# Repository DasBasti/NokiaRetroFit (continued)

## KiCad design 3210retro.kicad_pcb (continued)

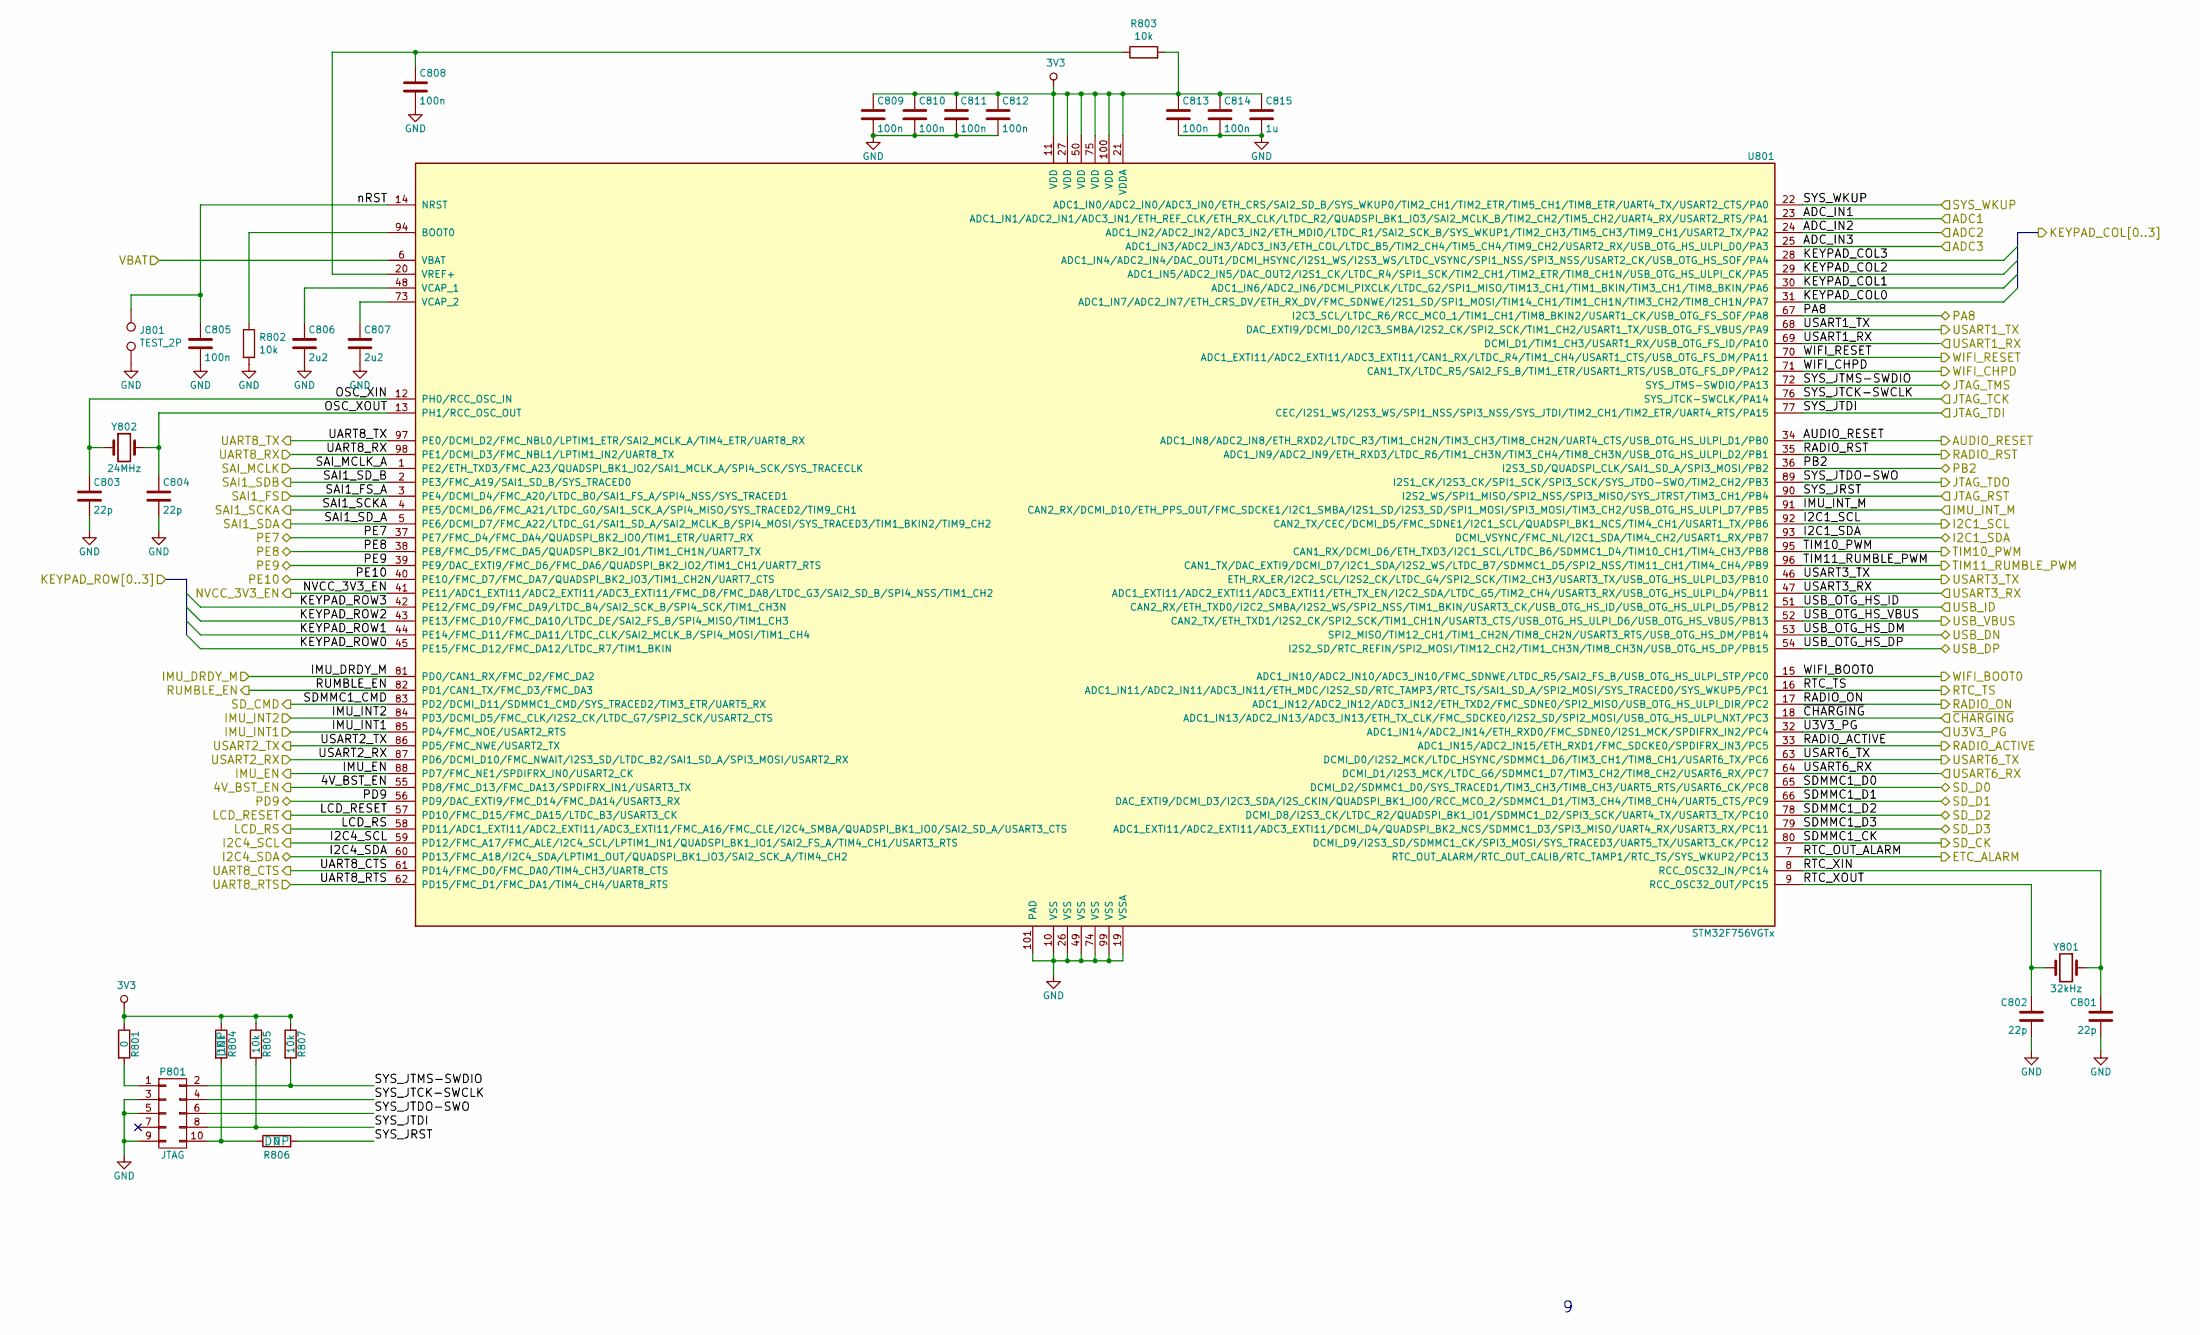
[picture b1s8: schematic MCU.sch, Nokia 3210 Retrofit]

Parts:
C801, C802, C803, C804: 22p; C_0402_NoSilk
C805, C808, C809, C810, C811, C812, C813, C814: 100n; C_0402_NoSilk
C806, C807: 2u2; C_0402_NoSilk
C815: 1u; C_0402_NoSilk
J801: TEST_2P; SolderWirePad_2x_0,8
P801: JTAG; Pin_Header_Straight_2x05_Pitch1.27mm
R801, R806: 0; R_0402_NoSilk
R802, R803, R804, R805, R807: 10k; R_0402_NoSilk
U801: STM32F756VGTx; TQFP-100-1EP_14x14mm_Pitch0.5mm
Y801: 32kHz; Crystal_SMD_2012-2pin_2.0x1.2mm
Y802: 24MHz; Crystal_SMD_2016-4pin_2.0x1.6mm

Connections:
3V3: C809.1, C810.1, C811.1, C812.1, C813.1, C814.1, C815.1, R801.1, R803.2, R804.1, R805.1, R807.1, U801.11 (VDD), U801.21 (VDDA), U801.27 (VDD), U801.50 (VDD), U801.75 (VDD), U801.100 (VDD); also elsewhere on the board
+5V: U801.52 (CAN2_TX/ETH_TXD1/I2S2_CK/SPI2_SCK/TIM1_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); also elsewhere on the board
/Audio Amplifier/AUDIO_I2C_SCL: U801.59 (PD12/FMC_A17/FMC_ALE/I2C4_SCL/LPTIM1_IN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); also elsewhere on the board
/Audio Amplifier/AUDIO_I2C_SDA: U801.60 (PD13/FMC_A18/I2C4_SDA/LPTIM1_OUT/QUADSP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); also elsewhere on the board
/Audio Amplifier/AUDIO_RESET: U801.34 (ADC1_IN8/ADC2_IN8/ETH_RXD2/LTDC_R3/TIM1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); also elsewhere on the board
/Audio Amplifier/RMBL_EN: U801.82 (PD1/CAN1_TX/FMC_D3/FMC_DA3); also elsewhere on the board
/Audio Amplifier/RMBL_PWM: U801.96 (CAN1_TX/DAC_EXTI9/DCMI_D7/I2C1_SDA/I2S2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); also elsewhere on the board
/Buttons and LEDs/KEYPAD_COL0: U801.31 (ADC1_IN7/ADC2_IN7/ETH_CRS_DV/ETH_RX_DV/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); also elsewhere on the board
/Buttons and LEDs/KEYPAD_COL1: U801.30 (ADC1_IN6/ADC2_IN6/DCMI_PIXCLK/LTDC_G2/S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); also elsewhere on the board
/Buttons and LEDs/KEYPAD_COL2: U801.29 (ADC1_IN5/ADC2_IN5/DAC_OUT2/I2S1_CK/LTDC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); also elsewhere on the board
/Buttons and LEDs/KEYPAD_COL3: U801.28 (ADC1_IN4/ADC2_IN4/DAC_OUT1/DCMI_HSYNC/I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); also elsewhere on the board
/Buttons and LEDs/KEYPAD_ROW0: U801.45 (PE15/FMC_D12/FMC_DA12/LTDC_R7/TIM1_BKIN); also elsewhere on the board
/Buttons and LEDs/KEYPAD_ROW1: U801.44 (PE14/FMC_D11/FMC_DA11/LTDC_CLK/SAI2_MCL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); also elsewhere on the board
/Buttons and LEDs/KEYPAD_ROW2: U801.43 (PE13/FMC_D10/FMC_DA10/LTDC_DE/SAI2_FS_B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); also elsewhere on the board
/Buttons and LEDs/KEYPAD_ROW3: U801.42 (PE12/FMC_D9/FMC_DA9/LTDC_B4/SAI2_SCK_B/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); also elsewhere on the board
/Buttons and LEDs/LEDPWM: U801.95 (CAN1_RX/DCMI_D6/ETH_TXD3/I2C1_SCL/LTDC_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); also elsewhere on the board
/Controller/4V_BST_EN: U801.55 (PD8/FMC_D13/FMC_DA13/SPDIFRX_IN1/USART3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); also elsewhere on the board
/Controller/ADC1: U801.23 (ADC1_IN1/ADC2_IN1/ADC3_IN1/ETH_REF_CLK/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); also elsewhere on the board
/Controller/ADC2: U801.24 (ADC1_IN2/ADC2_IN2/ADC3_IN2/ETH_MDIO/LTD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); also elsewhere on the board
/Controller/ADC3: U801.25 (ADC1_IN3/ADC2_IN3/ADC3_IN3/ETH_COL/LTDC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); also elsewhere on the board
/Controller/ETC_ALARM: U801.7 (RTC_OUT_ALARM/RTC_OUT_CALIB/RTC_TAMP1/R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); also elsewhere on the board
/Controller/I2C1_SCL: U801.92 (CAN2_TX/CEC/DCMI_D5/FMC_SDNE1/I2C1_SCL/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); also elsewhere on the board
/Controller/I2C1_SDA: U801.93 (DCMI_VSYNC/FMC_NL/I2C1_SDA/TIM4_CH2/USA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); also elsewhere on the board
/Controller/IMU_DRDY_M: U801.81 (PD0/CAN1_RX/FMC_D2/FMC_DA2); also elsewhere on the board
/Controller/IMU_EN: U801.88 (PD7/FMC_NE1/SPDIFRX_IN0/USART2_CK); also elsewhere on the board
/Controller/IMU_INT1: U801.85 (PD4/FMC_NOE/USART2_RTS); also elsewhere on the board
/Controller/IMU_INT2: U801.84 (PD3/DCMI_D5/FMC_CLK/I2S2_CK/LTDC_G7/SPI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); also elsewhere on the board
/Controller/IMU_INT_M: U801.91 (CAN2_RX/DCMI_D10/ETH_PPS_OUT/FMC_SDCKE1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); also elsewhere on the board
/Controller/JTAG_RST: R806.2, U801.90 (I2S2_WS/SPI1_MISO/SPI2_NSS/SPI3_MISO/SY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)
/Controller/JTAG_TCK: P801.4, U801.76 (SYS_JTCK-SWCLK/PA14)
/Controller/JTAG_TDI: P801.8, R805.2, U801.77 (CEC/I2S1_WS/I2S3_WS/SPI1_NSS/SPI3_NSS/S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)
/Controller/JTAG_TDO: P801.6, U801.89 (I2S1_CK/I2S3_CK/SPI1_SCK/SPI3_SCK/SYS_J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)
/Controller/JTAG_TMS: P801.2, R807.2, U801.72 (SYS_JTMS-SWDIO/PA13)
/Controller/LCD_RESET: U801.57 (PD10/FMC_D15/FMC_DA15/LTDC_B3/USART3_CK); also elsewhere on the board
/Controller/LCD_RS: U801.58 (PD11/ADC1_EXTI11/ADC2_EXTI11/ADC3_EXTI1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); also elsewhere on the board
/Controller/NVCC_3V3_EN: U801.41 (PE11/ADC1_EXTI11/ADC2_EXTI11/ADC3_EXTI1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); also elsewhere on the board
/Controller/OSC_XIN: C803.1, U801.12 (PH0/RCC_OSC_IN), Y802.1
/Controller/OSC_XOUT: C804.1, U801.13 (PH1/RCC_OSC_OUT), Y802.2
/Controller/PA8: U801.67 (I2C3_SCL/LTDC_R6/RCC_MCO_1/TIM1_CH1/TIM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); also elsewhere on the board
/Controller/PB2: U801.36 (I2S3_SD/QUADSPI_CLK/SAI1_SD_A/SPI3_MOSI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); also elsewhere on the board
/Controller/PD9: U801.56 (PD9/DAC_EXTI9/FMC_D14/FMC_DA14/USART3_RX); also elsewhere on the board
/Controller/PE7: U801.37 (PE7/FMC_D4/FMC_DA4/QUADSPI_BK2_IO0/TIM1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); also elsewhere on the board
/Controller/PE8: U801.38 (PE8/FMC_D5/FMC_DA5/QUADSPI_BK2_IO1/TIM1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); also elsewhere on the board
/Controller/PE9: U801.39 (PE9/DAC_EXTI9/FMC_D6/FMC_DA6/QUADSPI_BK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); also elsewhere on the board
/Controller/PE10: U801.40 (PE10/FMC_D7/FMC_DA7/QUADSPI_BK2_IO3/TIM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); also elsewhere on the board
/Controller/RADIO_RST: U801.35 (ADC1_IN9/ADC2_IN9/ETH_RXD3/LTDC_R6/TIM1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); also elsewhere on the board
/Controller/RTC_TS: U801.16 (ADC1_IN11/ADC2_IN11/ADC3_IN11/ETH_MDC/I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); also elsewhere on the board
/Controller/RTC_XIN: C801.1, U801.8 (RCC_OSC32_IN/PC14), Y801.1
/Controller/RTC_XOUT: C802.1, U801.9 (RCC_OSC32_OUT/PC15), Y801.2
/Controller/SAI1_FS: U801.3 (PE4/DCMI_D4/FMC_A20/LTDC_B0/SAI1_FS_A/S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); also elsewhere on the board
/Controller/SAI1_SCKA: U801.4 (PE5/DCMI_D6/FMC_A21/LTDC_G0/SAI1_SCK_A/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); also elsewhere on the board
/Controller/SAI1_SDA: U801.5 (PE6/DCMI_D7/FMC_A22/LTDC_G1/SAI1_SD_A/S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); also elsewhere on the board
/Controller/SAI1_SDB: U801.2 (PE3/FMC_A19/SAI1_SD_B/SYS_TRACED0); also elsewhere on the board
/Controller/SAI_MCLK: U801.1 (PE2/ETH_TXD3/FMC_A23/QUADSPI_BK1_IO2/SA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); also elsewhere on the board
/Controller/SD_CK: U801.80 (DCMI_D9/I2S3_SD/SDMMC1_CK/SPI3_MOSI/SYS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); also elsewhere on the board
/Controller/SD_CMD: U801.83 (PD2/DCMI_D11/SDMMC1_CMD/SYS_TRACED2/TIM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); also elsewhere on the board
/Controller/SD_D0: U801.65 (DCMI_D2/SDMMC1_D0/SYS_TRACED1/TIM3_CH3/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); also elsewhere on the board
/Controller/SD_D1: U801.66 (DAC_EXTI9/DCMI_D3/I2C3_SDA/I2S_CKIN/QUA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); also elsewhere on the board
/Controller/SD_D2: U801.78 (DCMI_D8/I2S3_CK/LTDC_R2/QUADSPI_BK1_IO1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); also elsewhere on the board
/Controller/SD_D3: U801.79 (ADC1_EXTI11/ADC2_EXTI11/ADC3_EXTI11/DCM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); also elsewhere on the board
/Controller/SYS_WKUP: U801.22 (ADC1_IN0/ADC2_IN0/ADC3_IN0/ETH_CRS/SAI2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); also elsewhere on the board
/Controller/USART1_TX: U801.68 (DAC_EXTI9/DCMI_D0/I2C3_SMBA/I2S2_CK/SPI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); also elsewhere on the board
/Controller/USART3_RX: U801.47 (ADC1_EXTI11/ADC2_EXTI11/ADC3_EXTI11/ETH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); also elsewhere on the board
/Controller/USART3_TX: U801.46 (ETH_RX_ER/I2C2_SCL/I2S2_CK/LTDC_G4/SPI2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); also elsewhere on the board
/Controller/USART6_RX: U801.64 (DCMI_D1/I2S3_MCK/LTDC_G6/SDMMC1_D7/TIM3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); also elsewhere on the board
/Controller/USART6_TX: U801.63 (DCMI_D0/I2S2_MCK/LTDC_HSYNC/SDMMC1_D6/T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); also elsewhere on the board
/Controller/USB_DN: U801.53 (SPI2_MISO/TIM12_CH1/TIM1_CH2N/TIM8_CH2N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); also elsewhere on the board
/Controller/USB_DP: U801.54 (I2S2_SD/RTC_REFIN/SPI2_MOSI/TIM12_CH2/T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); also elsewhere on the board
/Controller/USB_ID: U801.51 (CAN2_RX/ETH_TXD0/I2C2_SMBA/I2S2_WS/SPI2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); also elsewhere on the board
/Controller/VBAT: U801.6 (VBAT); also elsewhere on the board
/Controller/WIFI_BOOT0: U801.15 (ADC1_IN10/ADC2_IN10/ADC3_IN10/FMC_SDNWE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); also elsewhere on the board
/Controller/WIFI_CHPD: U801.71 (CAN1_TX/LTDC_R5/SAI2_FS_B/TIM1_ETR/USAR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); also elsewhere on the board
/Controller/WIFI_RESET: U801.70 (ADC1_EXTI11/ADC2_EXTI11/ADC3_EXTI11/CAN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); also elsewhere on the board
/Controller/nRST: C805.1, J801.1, U801.14 (NRST)
/Controller/~CHARGING: U801.18 (ADC1_IN13/ADC2_IN13/ADC3_IN13/ETH_TX_CL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); also elsewhere on the board
/Power and Battery/3V3_PG: U801.32 (ADC1_IN14/ADC2_IN14/ETH_RXD0/FMC_SDNE0/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); also elsewhere on the board
/Radio Module, GPS and SIM/ACTIVE: U801.33 (ADC1_IN15/ADC2_IN15/ETH_RXD1/FMC_SDCKE0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); also elsewhere on the board
/Radio Module, GPS and SIM/AT_UART_CTS: U801.62 (PD15/FMC_D1/FMC_DA1/TIM4_CH4/UART8_RTS); also elsewhere on the board
/Radio Module, GPS and SIM/AT_UART_RTS: U801.61 (PD14/FMC_D0/FMC_DA0/TIM4_CH3/UART8_CTS); also elsewhere on the board
/Radio Module, GPS and SIM/AT_UART_RX: U801.97 (PE0/DCMI_D2/FMC_NBL0/LPTIM1_ETR/SAI2_MC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); also elsewhere on the board
/Radio Module, GPS and SIM/AT_UART_TX: U801.98 (PE1/DCMI_D3/FMC_NBL1/LPTIM1_IN2/UART8_TX); also elsewhere on the board
/Radio Module, GPS and SIM/GPS_TX: U801.69 (DCMI_D1/TIM1_CH3/USART1_RX/USB_OTG_FS_I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); also elsewhere on the board
/Radio Module, GPS and SIM/HST_RX: U801.86 (PD5/FMC_NWE/USART2_TX); also elsewhere on the board
/Radio Module, GPS and SIM/HST_TX: U801.87 (PD6/DCMI_D10/FMC_NWAIT/I2S3_SD/LTDC_B2/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); also elsewhere on the board
/Radio Module, GPS and SIM/ON: U801.17 (ADC1_IN12/ADC2_IN12/ADC3_IN12/ETH_TXD2/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); also elsewhere on the board
GND: C801.2, C802.2, C803.2, C804.2, C805.2, C806.2, C807.2, C808.2, C809.2, C810.2, C811.2, C812.2, C813.2, C814.2, C815.2, J801.2, P801.3, P801.5, P801.9, R802.2, U801.10 (VSS), U801.19 (VSSA), U801.26 (VSS), U801.49 (VSS), U801.74 (VSS), U801.99 (VSS), U801.101 (PAD); also elsewhere on the board
unnamed: C806.1, U801.48 (VCAP_1)
unnamed: C807.1, U801.73 (VCAP_2)
unnamed: C808.1, R803.1, U801.20 (VREF+)
unnamed: P801.1, R801.2
unnamed: P801.10, R804.2, R806.1
unnamed: R802.1, U801.94 (BOOT0)

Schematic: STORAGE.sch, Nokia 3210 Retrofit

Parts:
J1101: MICRO_SD_HINGE; microSD_Card_Receptacle_Wuerth_693072010801

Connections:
/Controller/SD_CK: J1101.5 (CLK); also elsewhere on the board
/Controller/SD_CMD: J1101.3 (CMD); also elsewhere on the board
/Controller/SD_D0: J1101.7 (DAT0); also elsewhere on the board
/Controller/SD_D1: J1101.8 (DAT1); also elsewhere on the board
/Controller/SD_D2: J1101.1 (DAT2); also elsewhere on the board
/Controller/SD_D3: J1101.2 (CD/DAT3); also elsewhere on the board
GND: J1101.6 (VSS), J1101.9 (GND1), J1101.10 (GND2), J1101.11 (GND3), J1101.12 (GND4); also elsewhere on the board
NVCC_3V3: J1101.4 (VDD); also elsewhere on the board

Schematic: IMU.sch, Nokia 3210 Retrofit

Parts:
C1308: 10n; C_0402_NoSilk
C1309: 100n; C_0402_NoSilk
U1301: LSM9DS1; LGA-24L_3x3.5mm_Pitch0.43mm

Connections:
/Audio Amplifier/AUDIO_I2C_SCL: U1301.2 (SCL/SPC); also elsewhere on the board
/Audio Amplifier/AUDIO_I2C_SDA: U1301.4 (SDA/SDI/SDO); also elsewhere on the board
/Controller/IMU_DRDY_M: U1301.9 (DRDY_M); also elsewhere on the board
/Controller/IMU_EN: U1301.13 (DEN_A/G); also elsewhere on the board
/Controller/IMU_INT1: U1301.11 (INT1_A/G); also elsewhere on the board
/Controller/IMU_INT2: U1301.12 (INT2_A/G); also elsewhere on the board
/Controller/IMU_INT_M: U1301.10 (INT_M); also elsewhere on the board
GND: C1308.2, C1309.2, U1301.5 (SDO_AG), U1301.6 (SDO_M), U1301.14 (RES), U1301.15 (RES), U1301.16 (RES), U1301.17 (RES), U1301.18 (RES), U1301.19 (GND), U1301.20 (GND); also elsewhere on the board
NVCC_3V3: U1301.1 (VDDIO), U1301.3 (VDDIO), U1301.7 (CS_A/G), U1301.8 (CS_M), U1301.22 (VDD), U1301.23 (VDD); also elsewhere on the board
unnamed: C1308.1, U1301.21 (CAP)
unnamed: C1309.1, U1301.24 (C1)

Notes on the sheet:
LSB for I2C address

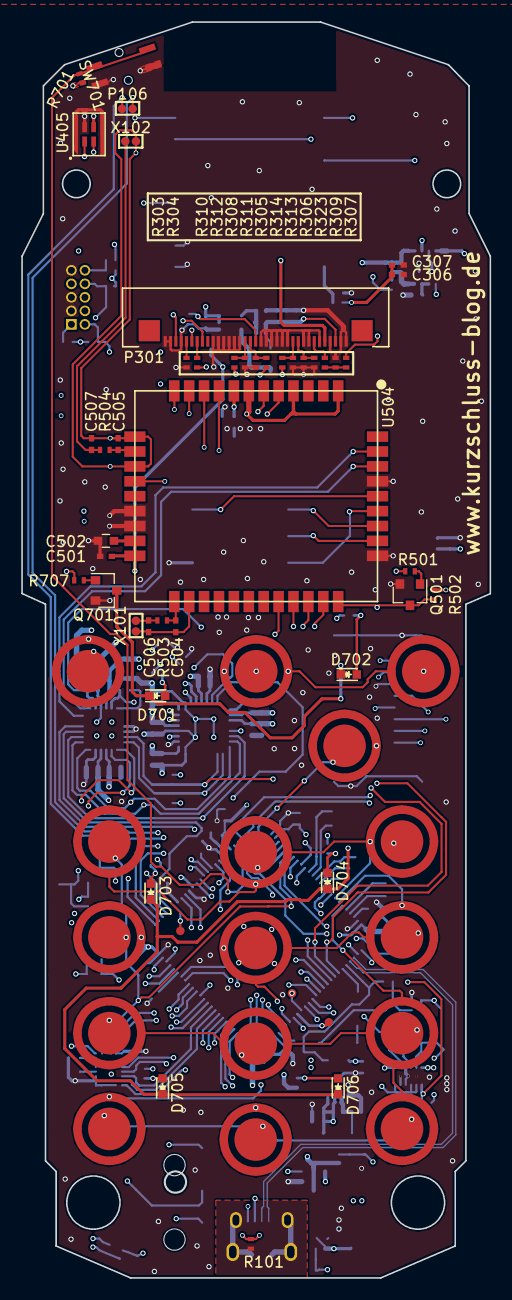
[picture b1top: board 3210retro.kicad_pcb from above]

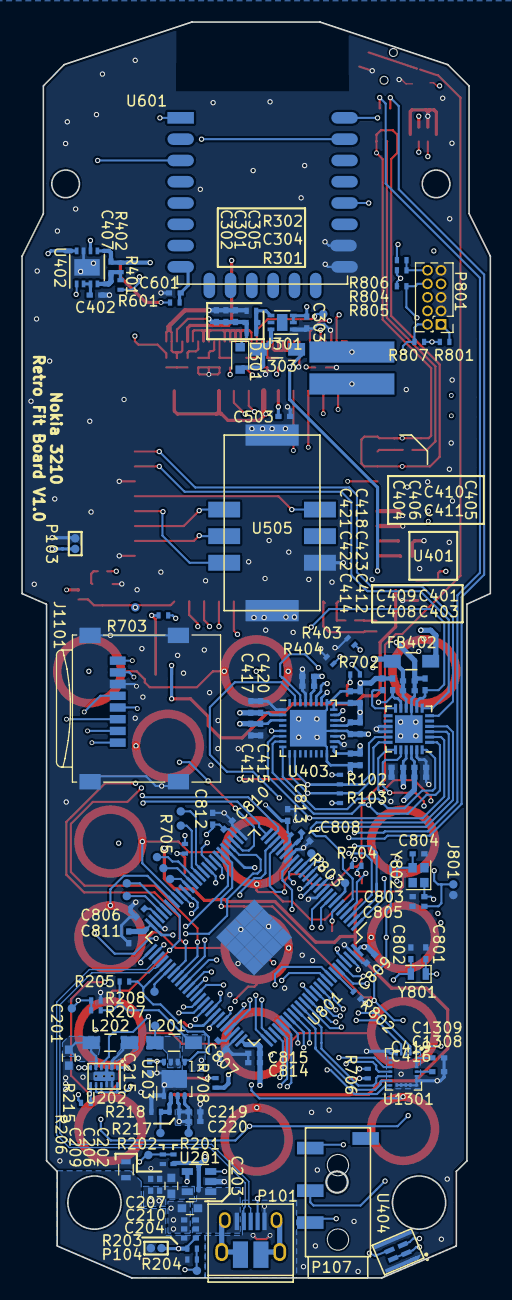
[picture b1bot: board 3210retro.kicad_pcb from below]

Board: 6 copper layers, 44.0 x 118.0 mm, 198 parts (121 on the bottom side), 155 nets.

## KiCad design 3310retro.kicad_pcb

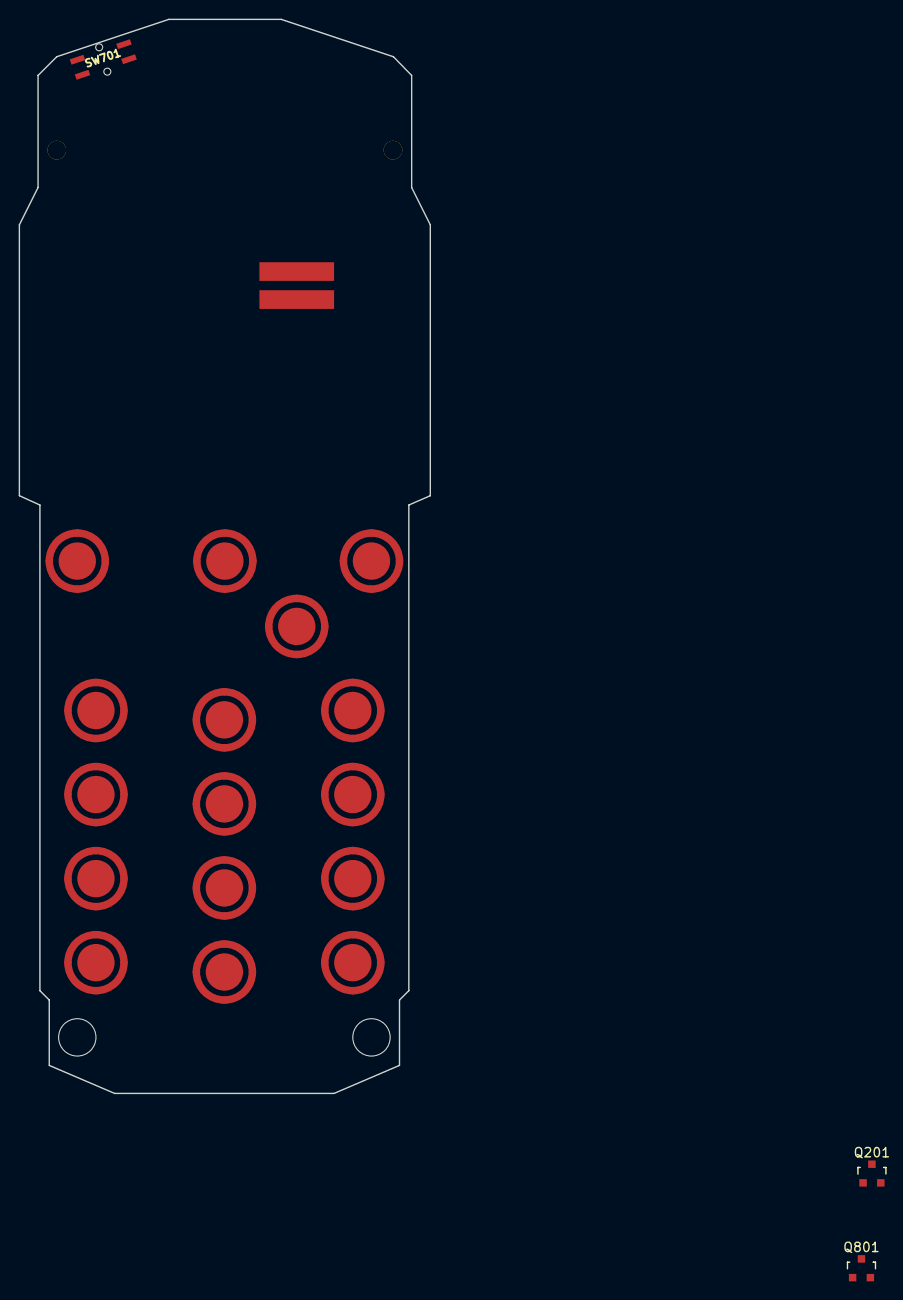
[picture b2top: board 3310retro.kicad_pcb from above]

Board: 2 copper layers, 44.0 x 115.0 mm, 20 parts (0 on the bottom side), 9 nets, no tracks yet.

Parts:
P109: Rumble_Pads
Q201: BC817-40; SOT-23
Q801: BSS138; SOT-23
SW701: SW_PUSH; TS-015A
SW702: C; Foil_Button
SW703: 1; Foil_Button
SW704: 4ghi; Foil_Button
SW705: 7pqrs; Foil_Button
SW706: -; Foil_Button
SW707: 2abc; Foil_Button
SW708: 5jkl; Foil_Button
SW709: 8tuv; Foil_Button
SW710: UP; Foil_Button
SW711: 3def; Foil_Button
SW712: 6mno; Foil_Button
SW713: 9wxyz; Foil_Button
SW714: *+; Foil_Button
SW715: DOWN; Foil_Button
SW716: 0space; Foil_Button
SW717: #up; Foil_Button

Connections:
/Buttons and LEDs/COL_1: SW702.1, SW703.1, SW704.1, SW705.1
/Buttons and LEDs/COL_2: SW706.1, SW707.1, SW708.1, SW709.1
/Buttons and LEDs/COL_3: SW710.1, SW711.1, SW712.1, SW713.1
/Buttons and LEDs/COL_4: SW714.1, SW715.1, SW716.1, SW717.1
/Buttons and LEDs/ROW_1: SW702.2, SW706.2, SW710.2, SW714.2
/Buttons and LEDs/ROW_2: SW703.2, SW707.2, SW711.2, SW715.2
/Buttons and LEDs/ROW_3: SW704.2, SW708.2, SW712.2, SW716.2
/Buttons and LEDs/ROW_4: SW705.2, SW709.2, SW713.2, SW717.2
GND: Q201.2, Q801.2, SW701.1

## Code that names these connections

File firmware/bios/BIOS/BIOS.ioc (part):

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Mcu.Name=STM32F756VGTx
Mcu.Package=LQFP100
Mcu.UserName=STM32F756VGTx
PA0/WKUP.GPIOParameters=GPIO_Label
PA0/WKUP.GPIO_Label=SYS_WKUP
PA0/WKUP.Mode=SYS_WakeUp0
PA0/WKUP.Signal=SYS_WKUP1
PA1.Signal=ADCx_IN1
PA10.Mode=Asynchronous
PA10.Signal=USART1_RX
PA11.GPIOParameters=GPIO_Label
PA11.GPIO_Label=WIFI_RESET
PA11.Signal=GPIO_Output
PA12.GPIOParameters=GPIO_Label
PA12.GPIO_Label=WIFI_CHPD
PA12.Signal=GPIO_Output
PA13.Mode=JTAG_5_pins
PA13.Signal=SYS_JTMS-SWDIO
PA14.Mode=JTAG_5_pins
PA14.Signal=SYS_JTCK-SWCLK
PA15.Mode=JTAG_5_pins
PA15.Signal=SYS_JTDI
PA2.Signal=ADCx_IN2
PA3.Signal=ADCx_IN3
PA4.GPIOParameters=GPIO_Label
PA4.GPIO_Label=KEYPAD_COL3
PA4.Signal=GPIO_Output
PA5.GPIOParameters=GPIO_Label
PA5.GPIO_Label=KEYPAD_COL2
PA5.Signal=GPIO_Output
PA6.GPIOParameters=GPIO_Label
PA6.GPIO_Label=KEYPAD_COL1
PA6.Signal=GPIO_Output
PA7.GPIOParameters=GPIO_Label
PA7.GPIO_Label=KEYPAD_COL0
PA7.Signal=GPIO_Output
PA9.Mode=Asynchronous
PA9.Signal=USART1_TX
PB0.GPIOParameters=GPIO_Label
PB0.GPIO_Label=AUDIO_INT
PB0.Signal=GPIO_Input
PB1.GPIOParameters=GPIO_Label
PB1.GPIO_Label=RADIO_RST
PB1.Signal=GPIO_Output
PB10.Mode=Asynchronous
PB10.Signal=USART3_TX
PB11.Mode=Asynchronous
PB11.Signal=USART3_RX
PB12.Mode=OTG/Dual-Role-Device-FS
PB12.Signal=USB_OTG_HS_ID
PB13.Mode=Activate_VBUS_FS
PB13.Signal=USB_OTG_HS_VBUS
PB14.Mode=OTG/Dual-Role-Device-FS
PB14.Signal=USB_OTG_HS_DM
PB15.Mode=OTG/Dual-Role-Device-FS
PB15.Signal=USB_OTG_HS_DP
PB3.Mode=JTAG_5_pins
PB3.Signal=SYS_JTDO-SWO
PB4.Mode=JTAG_5_pins
PB4.Signal=SYS_JTRST
PB5.GPIOParameters=GPIO_Label
PB5.GPIO_Label=IMU_INT_M
PB5.Signal=GPIO_Input
PB6.Mode=I2C
PB6.Signal=I2C1_SCL
PB7.Mode=I2C
PB7.Signal=I2C1_SDA
PB8.GPIOParameters=GPIO_Label
PB8.GPIO_Label=TIM10_PWM
PB8.Signal=S_TIM10_CH1
PB9.GPIOParameters=GPIO_Label
PB9.GPIO_Label=TIM11_RUMBLE_PWM
PB9.Signal=S_TIM11_CH1
PC0.GPIOParameters=GPIO_Label
PC0.GPIO_Label=WIFI_BOOT0
PC0.Signal=GPIO_Output
PC1.Mode=Timestamp enabled - Input Enabled to TS
PC1.Signal=RTC_TS
PC10.Mode=SD_4_bits_Wide_bus
PC10.Signal=SDMMC1_D2
PC11.Mode=SD_4_bits_Wide_bus
PC11.Signal=SDMMC1_D3
PC12.Mode=SD_4_bits_Wide_bus
PC12.Signal=SDMMC1_CK
PC13.Mode=AlarmB_RoutedAF
PC13.Signal=RTC_OUT_ALARM
PC14/OSC32_IN.Mode=LSE-External-Oscillator
PC14/OSC32_IN.Signal=RCC_OSC32_IN
PC15/OSC32_OUT.Mode=LSE-External-Oscillator
PC15/OSC32_OUT.Signal=RCC_OSC32_OUT
PC2.GPIOParameters=GPIO_Label
PC2.GPIO_Label=RADIO_ON
PC2.Signal=GPIO_Output
PC3.GPIOParameters=GPIO_Label
PC3.GPIO_Label=CHARGING
PC3.Signal=GPIO_Input
PC4.GPIOParameters=GPIO_Label
PC4.GPIO_Label=U3V3_PG
PC4.Signal=GPIO_Input
PC5.GPIOParameters=GPIO_Label
PC5.GPIO_Label=RADIO_ACTIVE
PC5.Signal=GPIO_Output
PC6.Mode=Asynchronous
PC6.Signal=USART6_TX
PC7.Mode=Asynchronous
PC7.Signal=USART6_RX
PC8.Mode=SD_4_bits_Wide_bus
PC8.Signal=SDMMC1_D0
PC9.Mode=SD_4_bits_Wide_bus
PC9.Signal=SDMMC1_D1
PD0.GPIOParameters=GPIO_Label
PD0.GPIO_Label=IMU_DRDY_M
PD0.Signal=GPIO_Input
PD1.GPIOParameters=GPIO_Label
PD1.GPIO_Label=RUMBLE_EN
PD1.Signal=GPIO_Output
PD10.GPIOParameters=GPIO_Label
PD10.GPIO_Label=LCD_RESET
PD10.Signal=GPIO_Output
PD11.GPIOParameters=GPIO_Label
PD11.GPIO_Label=LCD_RS
PD11.Signal=GPIO_Output
PD12.Mode=I2C
PD12.Signal=I2C4_SCL
PD13.Mode=I2C
PD13.Signal=I2C4_SDA
PD14.Mode=CTS_RTS
PD14.Signal=UART8_CTS
PD15.Mode=CTS_RTS
PD15.Signal=UART8_RTS
PD2.Mode=SD_4_bits_Wide_bus
PD2.Signal=SDMMC1_CMD
PD3.GPIOParameters=GPIO_Label
PD3.GPIO_Label=IMU_INT2
PD3.Signal=GPIO_Input
PD4.GPIOParameters=GPIO_Label
PD4.GPIO_Label=IMU_INT1
PD4.Signal=GPIO_Input
PD5.Mode=Asynchronous
PD5.Signal=USART2_TX
PD6.Mode=Asynchronous
PD6.Signal=USART2_RX
PD7.GPIOParameters=GPIO_Label
PD7.GPIO_Label=IMU_EN
PD7.Signal=GPIO_Output
PE0.Mode=Asynchronous
PE0.Signal=UART8_RX
PE1.Mode=Asynchronous
PE1.Signal=UART8_TX
PE11.GPIOParameters=GPIO_Label
PE11.GPIO_Label=NVCC_3V3_EN
PE11.Signal=GPIO_Output
PE12.GPIOParameters=GPIO_Label
PE12.GPIO_Label=KEYPAD_ROW3
PE12.Signal=GPIO_Input
PE13.GPIOParameters=GPIO_Label
PE13.GPIO_Label=KEYPAD_ROW2
PE13.Signal=GPIO_Input
PE14.GPIOParameters=GPIO_Label
PE14.GPIO_Label=KEYPAD_ROW1
PE14.Signal=GPIO_Input
PE15.GPIOParameters=GPIO_Label
PE15.GPIO_Label=KEYPAD_ROW0
PE15.Signal=GPIO_Input
PE2.Mode=SAI_A_MasterWithClock
PE2.Signal=SAI1_MCLK_A
PE3.Mode=SAI_B_SyncSlave
PE3.Signal=SAI1_SD_B
PE4.Mode=SAI_A_MasterWithClock
PE4.Signal=SAI1_FS_A
PE5.Mode=SAI_A_MasterWithClock
PE5.Signal=SAI1_SCK_A
PE6.Mode=SAI_A_MasterWithClock
PE6.Signal=SAI1_SD_A
PH0/OSC_IN.Mode=HSE-External-Oscillator
PH0/OSC_IN.Signal=RCC_OSC_IN
PH1/OSC_OUT.Mode=HSE-External-Oscillator
PH1/OSC_OUT.Signal=RCC_OSC_OUT
RCC.HSE_VALUE=24000000
RCC.SYSCLKFreq_VALUE=216000000
RCC.SYSCLKSource=RCC_SYSCLKSOURCE_PLLCLK
board=BIOS

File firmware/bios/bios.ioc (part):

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Mcu.Name=STM32F756VGTx
Mcu.Package=LQFP100
Mcu.UserName=STM32F756VGTx
PA0/WKUP.GPIOParameters=GPIO_Label
PA0/WKUP.GPIO_Label=SYS_WKUP
PA0/WKUP.Mode=SYS_WakeUp0
PA0/WKUP.Signal=SYS_WKUP1
PA1.Signal=ADCx_IN1
PA10.Mode=Asynchronous
PA10.Signal=USART1_RX
PA11.GPIOParameters=GPIO_Label
PA11.GPIO_Label=WIFI_RESET
PA11.Signal=GPIO_Output
PA12.GPIOParameters=GPIO_Label
PA12.GPIO_Label=WIFI_CHPD
PA12.Signal=GPIO_Output
PA13.Mode=JTAG_5_pins
PA13.Signal=SYS_JTMS-SWDIO
PA14.Mode=JTAG_5_pins
PA14.Signal=SYS_JTCK-SWCLK
PA15.Mode=JTAG_5_pins
PA15.Signal=SYS_JTDI
PA2.Signal=ADCx_IN2
PA3.Signal=ADCx_IN3
PA4.GPIOParameters=GPIO_Label
PA4.GPIO_Label=KEYPAD_COL3
PA4.Signal=GPIO_Output
PA5.GPIOParameters=GPIO_Label
PA5.GPIO_Label=KEYPAD_COL2
PA5.Signal=GPIO_Output
PA6.GPIOParameters=GPIO_Label
PA6.GPIO_Label=KEYPAD_COL1
PA6.Signal=GPIO_Output
PA7.GPIOParameters=GPIO_Label
PA7.GPIO_Label=KEYPAD_COL0
PA7.Signal=GPIO_Output
PA8.Mode=I2C
PA8.Signal=I2C3_SCL
PA9.Mode=Asynchronous
PA9.Signal=USART1_TX
PB1.GPIOParameters=GPIO_Label
PB1.GPIO_Label=RADIO_RST
PB1.Signal=GPIO_Output
PB10.Mode=Asynchronous
PB10.Signal=USART3_TX
PB11.Mode=Asynchronous
PB11.Signal=USART3_RX
PB12.Mode=OTG/Dual-Role-Device-FS
PB12.Signal=USB_OTG_HS_ID
PB13.Mode=Activate_VBUS_FS
PB13.Signal=USB_OTG_HS_VBUS
PB14.Mode=OTG/Dual-Role-Device-FS
PB14.Signal=USB_OTG_HS_DM
PB15.Mode=OTG/Dual-Role-Device-FS
PB15.Signal=USB_OTG_HS_DP
PB2.Mode=Single Bank 2
PB2.Signal=QUADSPI_CLK
PB3.Mode=JTAG_5_pins
PB3.Signal=SYS_JTDO-SWO
PB4.Mode=JTAG_5_pins
PB4.Signal=SYS_JTRST
PB5.GPIOParameters=GPIO_Label
PB5.GPIO_Label=IMU_INT_M
PB5.Signal=GPIO_Input
PB6.Mode=I2C
PB6.Signal=I2C1_SCL
PB7.Mode=I2C
PB7.Signal=I2C1_SDA
PB8.GPIOParameters=GPIO_Label
PB8.GPIO_Label=TIM10_PWM
PB8.Signal=S_TIM10_CH1
PB9.GPIOParameters=GPIO_Label
PB9.GPIO_Label=IMU_DRDY_M
PB9.Signal=GPIO_Input
PC0.GPIOParameters=GPIO_Label
PC0.GPIO_Label=WIFI_BOOT0
PC0.Signal=GPIO_Output
PC1.Mode=Timestamp enabled - Input Enabled to TS
PC1.Signal=RTC_TS
PC11.Mode=Single Bank 2
PC11.Signal=QUADSPI_BK2_NCS
PC12.Mode=SD_1_bit
PC12.Signal=SDMMC1_CK
PC13.Mode=AlarmB_RoutedAF
PC13.Signal=RTC_OUT_ALARM
PC14/OSC32_IN.Mode=LSE-External-Oscillator
PC14/OSC32_IN.Signal=RCC_OSC32_IN
PC15/OSC32_OUT.Mode=LSE-External-Oscillator
PC15/OSC32_OUT.Signal=RCC_OSC32_OUT
PC2.GPIOParameters=GPIO_Label
PC2.GPIO_Label=RADIO_ON
PC2.Signal=GPIO_Output
PC3.GPIOParameters=GPIO_Label
PC3.GPIO_Label=CHARGING
PC3.Signal=GPIO_Input
PC5.GPIOParameters=GPIO_Label
PC5.GPIO_Label=RADIO_ACTIVE
PC5.Signal=GPIO_Output
PC6.Mode=Asynchronous
PC6.Signal=USART6_TX
PC7.Mode=Asynchronous
PC7.Signal=USART6_RX
PC8.Mode=SD_1_bit
PC8.Signal=SDMMC1_D0
PC9.Mode=I2C
PC9.Signal=I2C3_SDA
PD10.GPIOParameters=GPIO_Label
PD10.GPIO_Label=LCD_RESET
PD10.Signal=GPIO_Output
PD11.GPIOParameters=GPIO_Label
PD11.GPIO_Label=LCD_RS
PD11.Signal=GPIO_Output
PD12.Mode=I2C
PD12.Signal=I2C4_SCL
PD13.Mode=I2C
PD13.Signal=I2C4_SDA
PD14.Mode=CTS_RTS
PD14.Signal=UART8_CTS
PD15.Mode=CTS_RTS
PD15.Signal=UART8_RTS
PD2.Mode=SD_1_bit
PD2.Signal=SDMMC1_CMD
PD3.GPIOParameters=GPIO_Label
PD3.GPIO_Label=IMU_INT2
PD3.Signal=GPIO_Input
PD4.GPIOParameters=GPIO_Label
PD4.GPIO_Label=IMU_INT1
PD4.Signal=GPIO_Input
PD5.Mode=Asynchronous
PD5.Signal=USART2_TX
PD6.Mode=Asynchronous
PD6.Signal=USART2_RX
PD7.GPIOParameters=GPIO_Label
PD7.GPIO_Label=IMU_EN
PD7.Signal=GPIO_Output
PE0.Mode=Asynchronous
PE0.Signal=UART8_RX
PE1.Mode=Asynchronous
PE1.Signal=UART8_TX
PE10.Mode=Single Bank 2
PE10.Signal=QUADSPI_BK2_IO3
PE12.GPIOParameters=GPIO_Label
PE12.GPIO_Label=KEYPAD_ROW3
PE12.Signal=GPIO_Input
PE13.GPIOParameters=GPIO_Label
PE13.GPIO_Label=KEYPAD_ROW2
PE13.Signal=GPIO_Input
PE14.GPIOParameters=GPIO_Label
PE14.GPIO_Label=KEYPAD_ROW1
PE14.Signal=GPIO_Input
PE15.GPIOParameters=GPIO_Label
PE15.GPIO_Label=KEYPAD_ROW0
PE15.Signal=GPIO_Input
PE2.Mode=SAI_A_MasterWithClock
PE2.Signal=SAI1_MCLK_A
PE4.Mode=SAI_A_MasterWithClock
PE4.Signal=SAI1_FS_A
PE5.Mode=SAI_A_MasterWithClock
PE5.Signal=SAI1_SCK_A
PE6.Mode=SAI_A_MasterWithClock
PE6.Signal=SAI1_SD_A
PE7.Mode=Single Bank 2
PE7.Signal=QUADSPI_BK2_IO0
PE8.Mode=Single Bank 2
PE8.Signal=QUADSPI_BK2_IO1
PE9.Mode=Single Bank 2
PE9.Signal=QUADSPI_BK2_IO2
PH0/OSC_IN.Mode=HSE-External-Oscillator
PH0/OSC_IN.Signal=RCC_OSC_IN
PH1/OSC_OUT.Mode=HSE-External-Oscillator
PH1/OSC_OUT.Signal=RCC_OSC_OUT
RCC.HSE_VALUE=24000000
RCC.SYSCLKFreq_VALUE=216000000
RCC.SYSCLKSource=RCC_SYSCLKSOURCE_PLLCLK

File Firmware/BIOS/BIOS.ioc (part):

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Mcu.Name=STM32F429N(E-G-I)Hx
Mcu.Package=TFBGA216
Mcu.UserName=STM32F429NIHx
PA0/WKUP.Mode=Asynchronous
PA0/WKUP.Signal=UART4_TX
PA1.Mode=Asynchronous
PA1.Signal=UART4_RX
PA11.Mode=CTS_RTS
PA11.Signal=USART1_CTS
PA12.Mode=CTS_RTS
PA12.Signal=USART1_RTS
PA13.Mode=JTAG_5_pins
PA13.Signal=SYS_JTMS-SWDIO
PA14.Mode=JTAG_5_pins
PA14.Signal=SYS_JTCK-SWCLK
PA15.Mode=JTAG_5_pins
PA15.Signal=SYS_JTDI
PA2.Mode=Asynchronous
PA2.Signal=USART2_TX
PA4.Mode=Activate_SOF_FS
PA4.Signal=USB_OTG_HS_SOF
PA5.Signal=COMP_DAC2_group
PB11.Mode=I2C
PB11.Signal=I2C2_SDA
PB12.Mode=OTG/Dual-Role-Device-FS
PB12.Signal=USB_OTG_HS_ID
PB13.Mode=Activate_VBUS_FS
PB13.Signal=USB_OTG_HS_VBUS
PB14.Mode=OTG/Dual-Role-Device-FS
PB14.Signal=USB_OTG_HS_DM
PB15.Mode=OTG/Dual-Role-Device-FS
PB15.Signal=USB_OTG_HS_DP
PB3.Mode=JTAG_5_pins
PB3.Signal=SYS_JTDO-SWO
PB4.Mode=JTAG_5_pins
PB4.Signal=SYS_JTRST
PB6.Mode=Asynchronous
PB6.Signal=USART1_TX
PB7.Mode=Asynchronous
PB7.Signal=USART1_RX
PB8.Mode=I2C
PB8.Signal=I2C1_SCL
PB9.Mode=I2C
PB9.Signal=I2C1_SDA
PC0.Signal=ADCx_IN10
PC1.Signal=ADCx_IN11
PC10.Mode=SD_4_bits_Wide_bus
PC10.Signal=SDIO_D2
PC11.Mode=SD_4_bits_Wide_bus
PC11.Signal=SDIO_D3
PC12.Mode=SD_4_bits_Wide_bus
PC12.Signal=SDIO_CK
PC14/OSC32_IN.Mode=LSE-External-Oscillator
PC14/OSC32_IN.Signal=RCC_OSC32_IN
PC15/OSC32_OUT.Mode=LSE-External-Oscillator
PC15/OSC32_OUT.Signal=RCC_OSC32_OUT
PC2.Signal=ADCx_IN12
PC3.Signal=ADCx_IN13
PC4.Signal=ADCx_IN14
PC5.Signal=ADCx_IN15
PC8.Mode=SD_4_bits_Wide_bus
PC8.Signal=SDIO_D0
PC9.Mode=SD_4_bits_Wide_bus
PC9.Signal=SDIO_D1
PD0.Signal=FMC_D2_DA2
PD1.Signal=FMC_D3_DA3
PD10.Signal=FMC_D15_DA15
PD11.Signal=FMC_A16_CLE
PD12.Signal=FMC_A17_ALE
PD13.Signal=FMC_A18
PD14.Signal=FMC_D0_DA0
PD15.Signal=FMC_D1_DA1
PD2.Mode=SD_4_bits_Wide_bus
PD2.Signal=SDIO_CMD
PD3.Mode=CTS_Only
PD3.Signal=USART2_CTS
PD4.Signal=FMC_NOE
PD5.Signal=FMC_NWE
PD6.Mode=Asynchronous
PD6.Signal=USART2_RX
PD7.Mode=NorPsramChipSelect1_1
PD7.Signal=FMC_NE1
PD8.Signal=FMC_D13_DA13
PD9.Signal=FMC_D14_DA14
PE0.Signal=FMC_NBL0
PE1.Signal=FMC_NBL1
PE10.Signal=FMC_D7_DA7
PE11.Signal=FMC_D8_DA8
PE12.Signal=FMC_D9_DA9
PE13.Signal=FMC_D10_DA10
PE14.Signal=FMC_D11_DA11
PE15.Signal=FMC_D12_DA12
PE2.Signal=FMC_A23
PE3.Signal=FMC_A19
PE4.Signal=FMC_A20
PE5.Signal=FMC_A21
PE6.Signal=FMC_A22
PE7.Signal=FMC_D4_DA4
PE8.Signal=FMC_D5_DA5
PE9.Signal=FMC_D6_DA6
PF0.Signal=FMC_A0
PF1.Signal=FMC_A1
PF11.Signal=FMC_SDNRAS
PF12.Signal=FMC_A6
PF13.Signal=FMC_A7
PF14.Signal=FMC_A8
PF15.Signal=FMC_A9
PF2.Signal=FMC_A2
PF3.Signal=FMC_A3
PF4.Signal=FMC_A4
PF5.Signal=FMC_A5
PF6.Mode=Asynchronous
PF6.Signal=UART7_RX
PF7.Mode=Asynchronous
PF7.Signal=UART7_TX
PG0.Signal=FMC_A10
PG1.Signal=FMC_A11
PG13.Signal=FMC_A24
PG14.Signal=FMC_A25
PG15.Signal=FMC_SDNCAS
PG2.Signal=FMC_A12
PG3.Signal=FMC_A13
PG4.Signal=FMC_A14_BA0
PG5.Signal=FMC_A15_BA1
PG8.Signal=FMC_SDCLK
PG9.Signal=GPXTI9
PH0/OSC_IN.Mode=HSE-External-Oscillator
PH0/OSC_IN.Signal=RCC_OSC_IN
PH1/OSC_OUT.Mode=HSE-External-Oscillator
PH1/OSC_OUT.Signal=RCC_OSC_OUT
PH2.Mode=SdramChipSelect1_1
PH2.Signal=FMC_SDCKE0
PH3.Mode=SdramChipSelect1_1
PH3.Signal=FMC_SDNE0
PH4.Mode=I2C
PH4.Signal=I2C2_SCL
PH5.Signal=FMC_SDNWE
PI0.Mode=Half_Duplex_Master
PI0.Signal=I2S2_WS
PI1.Mode=Half_Duplex_Master
PI1.Signal=I2S2_CK
PI3.Mode=Half_Duplex_Master
PI3.Signal=I2S2_SD
RCC.HSE_VALUE=25000000
RCC.SYSCLKFreq_VALUE=120000000
RCC.SYSCLKSource=RCC_SYSCLKSOURCE_PLLCLK
board=BIOS

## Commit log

2016-12-17 Initial schematics of Nokia Retrofit Board
    - Power available:
    * USB_VBUS
    * VBAT
    * 4V
    * 3V3
    - Display: SPI 1.44"
2016-12-17 Schematics: - Added STZM32 MCU for the CPU kernel - Added ESP8266 for WiFi Subsheet
    Firmware:
    - Generated BIOS configuration for CubeMX
2016-12-17 current version of the schematics. Audio circuits are still missing.
    Audio curcuit topology
    Audio from cellphone module is routed to STM
    Audio from microphone is routed to STM
    STM processes audio and routes microphone data to cellphone module
    STM processes audio and routes cellphone audio to amplifier
    analog multiplexer can switch route from mic directly to cellphone module and module to speaker
2016-12-20 added Ti WL1807/1837 Module for WLAN and Bluetooth. added Test Points
2016-12-21 short schematics review and proposed changes
2016-12-22 moved to some Bus routing for serveral communication signals on the top sheet. This reduces lines on the top sheet.
    Changed 4V boost converter circuit toi use TPS61046 for size reasons
2017-01-02 aktuelle Version
2017-01-26 display placement
    The placement of the display connector is set.
2017-01-27 added some audio circuitry
2017-01-30 New display Datasheet. 1.69" display fits perfectly into existing frame.
2017-01-30 Display datasheets added
2017-02-04 Prepare Display change
2017-03-01 Added Interface for OLED display
    Added Booster for 4V -> 15V
    Added bus for display data
2017-03-05 Removed WiFi Module added Footprints
2017-05-17 added i.MX7 schematic symbol ignore chinese files in Documentation folder
2017-05-18 Added i.MX test schematic
    Added PF3000 symbol
2017-05-18 Added Voltage symbols for i.mx7 schematic
2017-05-18 finished DDR3L RAM for 1GB with 2 banks
2017-05-21 Started STM32 Fanout
2017-05-21 placed leds and corrected measurements
2017-05-21 added footprint for i.mx7
    added footprint for i.mx7. Use global solder mask distance of 0mm to get
    between the balls
2017-05-26 Added some schematics for PMIC Added some Documentation for i.mx7
2017-06-07 moved firles around to submodules to keep base repository for board and schematic design
2017-06-07 changed fp library to fit new folder structure
2017-06-07 Added schematic libraries to project file
2017-06-07 Make submodule tracking a branch
2017-06-07 Follow HEAD of Software repository
2017-06-11 started working on implementing i.MX7 core into base schematic
2017-06-11 fixed message telling to rescue PF3000 symbol while opening the schematic
2017-06-11 removed rescue lib from project
2017-06-14 Put key matrix into schematic. Using Keypad Peripheral of i.MX7
2017-06-15 Added SD card, eMMC, Display
2017-06-15 added emif06 datasheet added STORAGE subsheet revert WIFI.sch to version with WL1807MOD
2017-06-15 Connected WIFI subsheet with ESP8266 and WL1807MOD to SD2 Connected WL1807MOD Bluetoth UART to UART3 Connected A7 Module AT UART to UART6 Connected A7 GPS UART to UART5 Connected A7 HS download to UA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
2017-06-15 Moved USB into it's own subsheet shuffeld stuff around to make it less crammed
2017-06-15 renamed USB.sch to USB_IMU.sch added LSM9DS1 IMU to USB_IMU.sch and connected I2C2 bus shuffeld stuff around to make MCU.sch less crammed
2017-06-15 connected IMU signals to GPIO1_11 .. GPIO1_15
2017-06-16 updates lib_sch
2017-06-16 updates lib_sch Fised typo in net name
2017-06-16 removed USB.sch since it is obsolete
2017-06-17 modified adui circuit
2017-06-17 Added boost converter to battery circuit
2017-06-17 Added datasheet for TPS61021A
2017-06-17 updating submodule to latest
2017-06-17 Trying out a new Topsheet for page index, power tree diagram and a picture
2017-06-17 reverting to old sheet structure
2017-06-18 removed i.MX7_Test project since the i.MX7 kernel is transfered to the main schematic now
2017-06-18 updated schematic library
2017-06-18 modified README to reflect current status
2017-06-18 modified README
2017-06-18 updated software repository
2017-06-30 Prepare for two battery types NiMH battery for using the original battery pack LiPo battery for using long lasting modern battery
2017-07-02 Added power domains overview in POWER.sch subsheet fixed some power connections added datasheet for bq24401 charge controller updated schematic library
2017-07-02 Modified power domain overview to contain tree of power rails updated schematic lib reference
2017-07-02 Modified power nets Added table of contents
2017-07-02 updated software repo
2017-07-03 on battery charging circuit for NiMH battery
2017-07-08 Changed several voltage rail connections Removed non existing rails Added circuit for NiMH charging
2017-07-09 Changed SPI group voltage rail to 2V8 Changed EPDC2 group voltage rail to 2V8
2017-07-19 Created netlist with current components Foreward Annotation to Board
2017-07-25 added footprint for RAM, annotated sheets again
2017-08-13 Startet routing DDR3. Some things need to be cleared before routign process an begin
2017-08-15 Routing DDR3: connecting all signals
2017-08-15 Routing DDR3: placing caps close to power nets
2017-08-27 Added several via stacks for i.MX7 GND via Micro-Burried-Micro-Micro from GND_TOP to B.Cu
2017-08-27 more GND via stacks
2017-09-06 This branch moves from i.mx7 to STM32F4 CPU to be finished for Hackaday Prize 2017
2017-09-07 Modification for STM32 adaption
    For the Hackaday Prize 2017 I decided to switch to STM32 as CPU
    *Power system was modified to just contain the charge IC,
    *Boost converter for high voltage peripherals
    *Buck converter for 3V3 for CPU and switchable NVCC_3V3
    for peripherie
    CPU signals are routed and pinmux is done in firmware folder.
2017-09-08 Placed a lot of components and routed the audio codec
    The BGA of tha audio chipset is to small for regualr technology.
    We do not use all of the pins of the chip so we ignore the other
    pads and escape throug the balls of the other pad.
2017-09-10 Revision 1 of Layout
    6layer board
    through-hole via only (0.5/0.3mm drill)
    0.2mm track width
    https://hackaday.io/project/21263-nokia-3210-retro-fit-board/log/66914-prototype-pcb-done-there-comes-the-review
2017-09-14 Board modified to actual measurements
    * rumble motor was on the wrong side of the board. fixed
    * some drill holes where missing
    * moved voice mic to bottom side. top side is completely
    enclosed by the case
    * several small fixes
2017-09-14 update libraries
2017-09-14 fix for several signals
    * some signals where not routed out to the top sheet.
    * I2C signals where not connected.
    * moved imu subsheet to the other side of the mcu sheet to
    share I2C bus with audio
    * changed footprint of crystals to crystals I have
2017-09-14 Board Revision 1
    * Modified layout of I2C busses
    * Added Micro SD footprint back in
    * changed layout of crystals
2017-09-17 changed sound subsystem
    rerouted all the changed tracks
2017-09-18 worked on DRC messages
    * shuffeling tracks around to avoid vias
    * shuffeling vias around to avoid tracks
2017-09-24 finalized borad further
    placed more GND vias
    make 4V_BST switchable
    connect GND and GNDREF through resistor
2017-11-25 Current version that was ordered as board version 1
2017-11-27 Revert "Current version that was ordered as board version 1"
    This reverts commit 2e223613ce4d310fd76aa4487f7c9213e834245a.
2017-11-27 Modified Layout of U202 and added 10uF capacitor to output of U202 3V3 net is set top be 3V
